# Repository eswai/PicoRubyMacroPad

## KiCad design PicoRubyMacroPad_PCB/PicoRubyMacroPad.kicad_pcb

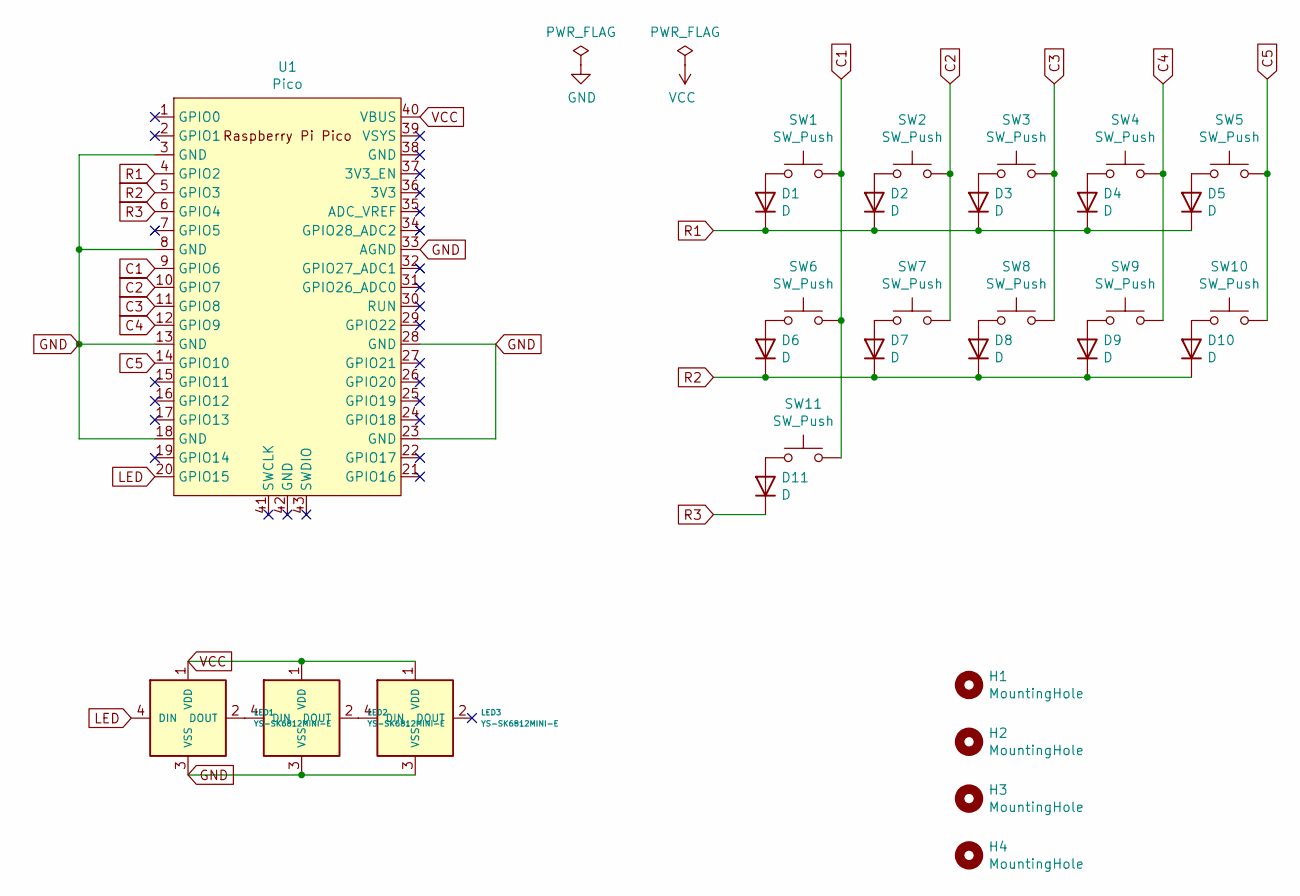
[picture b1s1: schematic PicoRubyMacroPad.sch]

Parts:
D1, D2, D3, D4, D5, D6, D7, D8, D9, D10, D11: D; D3_TH_SMD_v2
H1, H2, H3, H4: MountingHole; MountingHole_2.2mm_M2
LED1, LED2, LED3: YS-SK6812MINI-E
SW1, SW2, SW3, SW4, SW5, SW6, SW7, SW8, SW9, SW10: SW_Push; MXOnly-1U-NoLED
SW11: SW_Push; MXOnly-2.75U-ReversedStabilizers-NoLED
U1: Pico; RPi_Pico_SMD_TH

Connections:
C1: SW1.2, SW6.2, SW11.2, U1.9 (GPIO6)
C2: SW2.2, SW7.2, U1.10 (GPIO7)
C3: SW3.2, SW8.2, U1.11 (GPIO8)
C4: SW4.2, SW9.2, U1.12 (GPIO9)
C5: SW5.2, SW10.2, U1.14 (GPIO10)
GND: LED1.3 (VSS), LED2.3 (VSS), LED3.3 (VSS), U1.3 (GND), U1.8 (GND), U1.13 (GND), U1.18 (GND), U1.23 (GND), U1.28 (GND), U1.33 (AGND)
LED: LED1.4 (DIN), U1.20 (GPIO15)
unnamed: D1.2 (A), SW1.1
unnamed: D2.2 (A), SW2.1
unnamed: D3.2 (A), SW3.1
unnamed: D4.2 (A), SW4.1
unnamed: D5.2 (A), SW5.1
unnamed: D6.2 (A), SW6.1
unnamed: D7.2 (A), SW7.1
unnamed: D8.2 (A), SW8.1
unnamed: D9.2 (A), SW9.1
unnamed: D10.2 (A), SW10.1
unnamed: D11.2 (A), SW11.1
unnamed: LED1.2 (DOUT), LED2.4 (DIN)
unnamed: LED2.2 (DOUT), LED3.4 (DIN)
R1: D1.1 (K), D2.1 (K), D3.1 (K), D4.1 (K), D5.1 (K), U1.4 (GPIO2)
R2: D6.1 (K), D7.1 (K), D8.1 (K), D9.1 (K), D10.1 (K), U1.5 (GPIO3)
R3: D11.1 (K), U1.6 (GPIO4)
VCC: LED1.1 (VDD), LED2.1 (VDD), LED3.1 (VDD), U1.40 (VBUS)

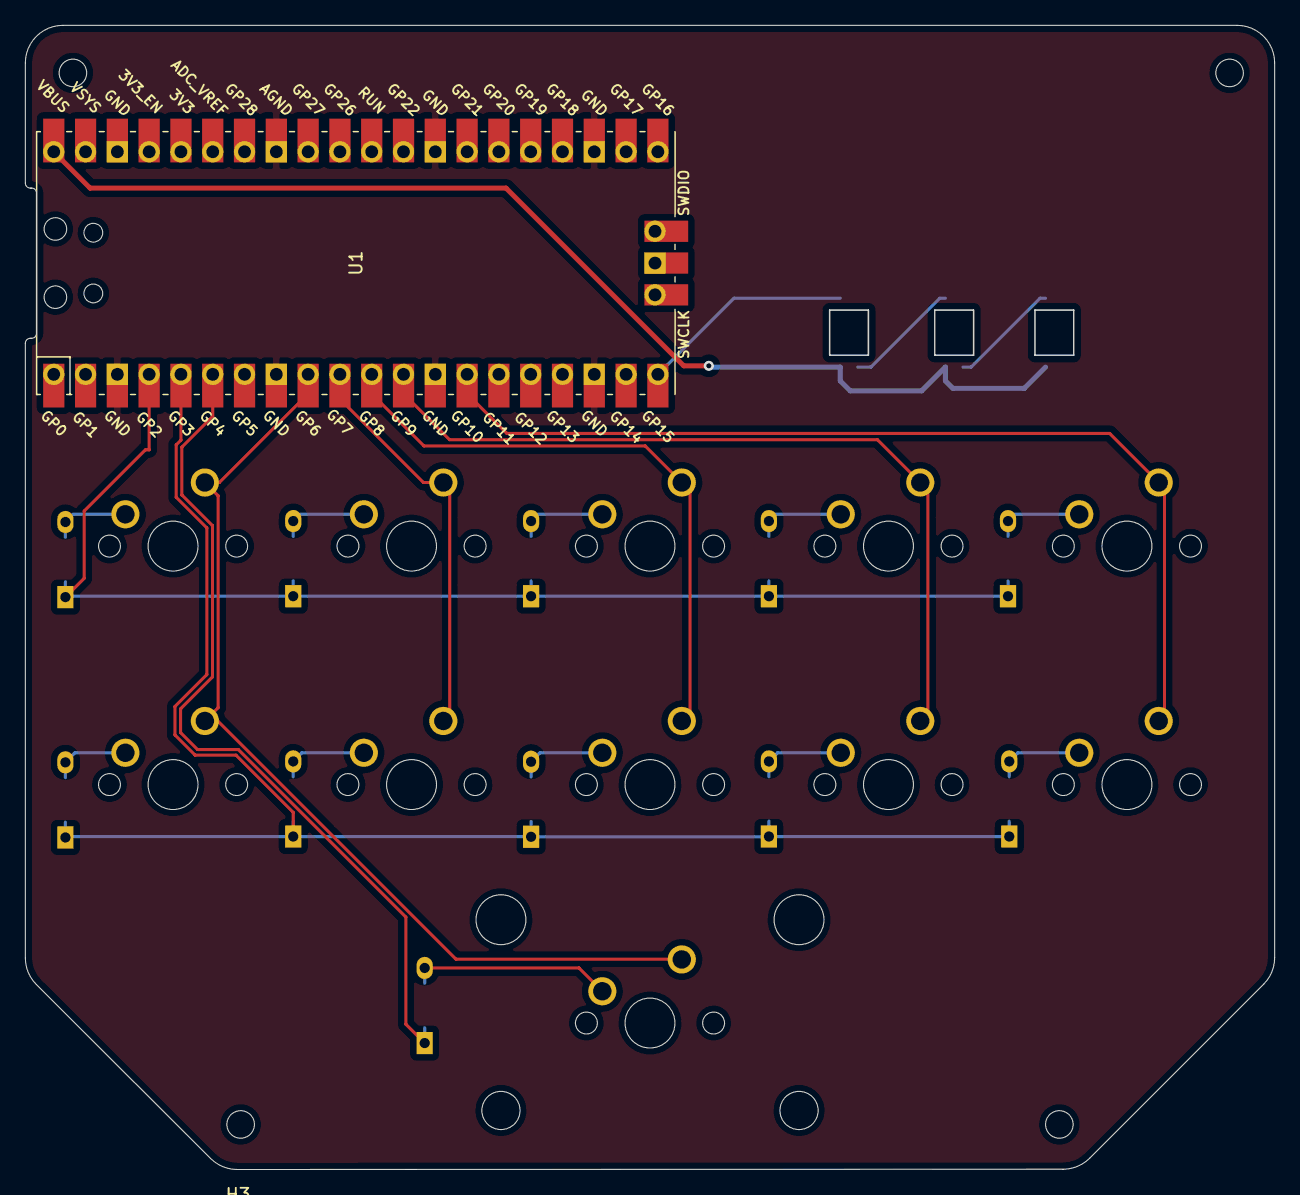
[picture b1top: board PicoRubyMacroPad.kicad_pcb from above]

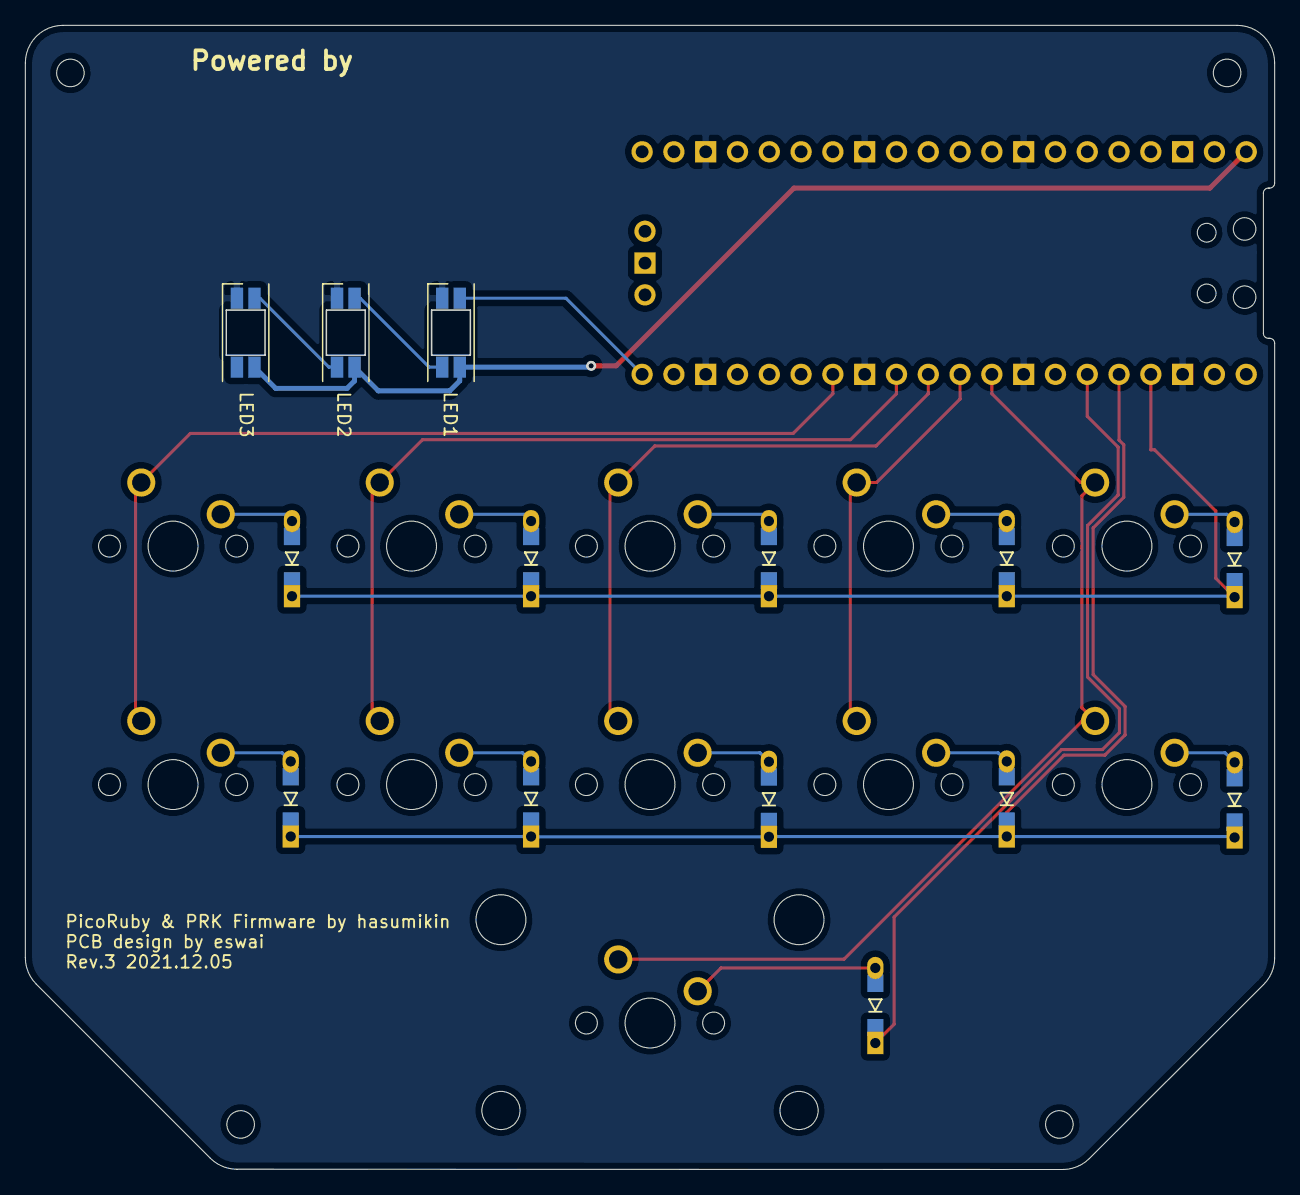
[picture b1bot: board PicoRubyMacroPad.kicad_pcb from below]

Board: 2 copper layers, 99.7 x 91.3 mm, 30 parts (14 on the bottom side), 24 nets.

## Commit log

2021-10-23 README
2021-10-23 PCB & Plate
2021-10-23 picture
2021-10-23 prk keymap file
2021-10-28 Fix to work on PRK Firmware 0.9.5
    - `while !$mutex do relinquish end` is no longer needed
    - The names of RGB#effect were changed to correspond to QMK
2021-12-05 A diode added for SW11
2021-12-05 A diode added
